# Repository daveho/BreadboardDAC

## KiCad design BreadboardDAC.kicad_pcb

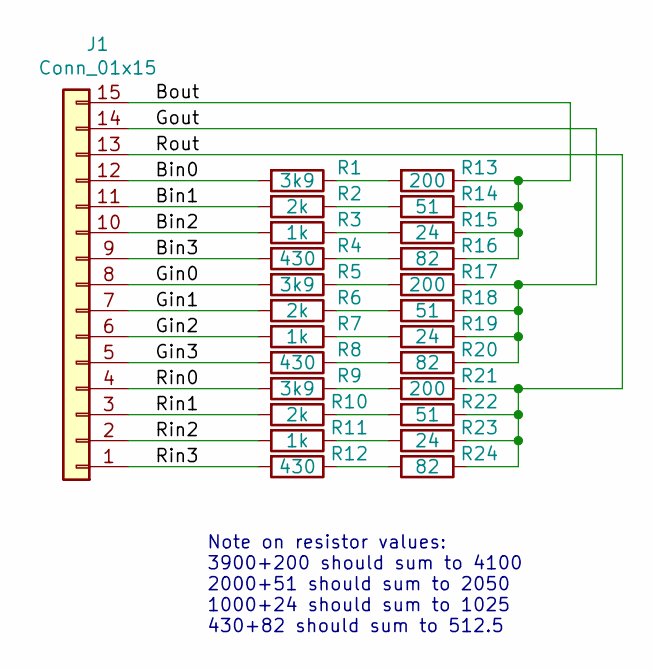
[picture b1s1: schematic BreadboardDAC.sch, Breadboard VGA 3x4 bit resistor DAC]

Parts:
J1: Conn_01x15; PinHeader_1x15_P2.54mm_Vertical
R1, R5, R9: 3k9; R_Axial_DIN0204_L3.6mm_D1.6mm_P2.54mm_Vertical
R2, R6, R10: 2k; R_Axial_DIN0204_L3.6mm_D1.6mm_P2.54mm_Vertical
R3, R7, R11: 1k; R_Axial_DIN0204_L3.6mm_D1.6mm_P2.54mm_Vertical
R4, R8, R12: 430; R_Axial_DIN0204_L3.6mm_D1.6mm_P2.54mm_Vertical
R13, R17, R21: 200; R_Axial_DIN0204_L3.6mm_D1.6mm_P2.54mm_Vertical
R14, R18, R22: 51; R_Axial_DIN0204_L3.6mm_D1.6mm_P2.54mm_Vertical
R15, R19, R23: 24; R_Axial_DIN0204_L3.6mm_D1.6mm_P2.54mm_Vertical
R16, R20, R24: 82; R_Axial_DIN0204_L3.6mm_D1.6mm_P2.54mm_Vertical

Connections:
/Bin0: J1.12, R1.2
/Bin1: J1.11, R2.2
/Bin2: J1.10, R3.2
/Bin3: J1.9, R4.2
/Bout: J1.15, R13.1, R14.1, R15.1, R16.1
/Gin0: J1.8, R5.2
/Gin1: J1.7, R6.2
/Gin2: J1.6, R7.2
/Gin3: J1.5, R8.2
/Gout: J1.14, R17.1, R18.1, R19.1, R20.1
/Rin0: J1.4, R9.2
/Rin1: J1.3, R10.2
/Rin2: J1.2, R11.2
/Rin3: J1.1, R12.2
/Rout: J1.13, R21.1, R22.1, R23.1, R24.1
unnamed: R1.1, R13.2
unnamed: R10.1, R22.2
unnamed: R11.1, R23.2
unnamed: R12.1, R24.2
unnamed: R2.1, R14.2
unnamed: R3.1, R15.2
unnamed: R4.1, R16.2
unnamed: R5.1, R17.2
unnamed: R6.1, R18.2
unnamed: R7.1, R19.2
unnamed: R8.1, R20.2
unnamed: R9.1, R21.2

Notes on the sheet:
Note on resistor values: 3900+200 should sum to 4100 2000+51 should sum to 2050 1000+24 should sum to 1025 430+82 should sum to 512.5

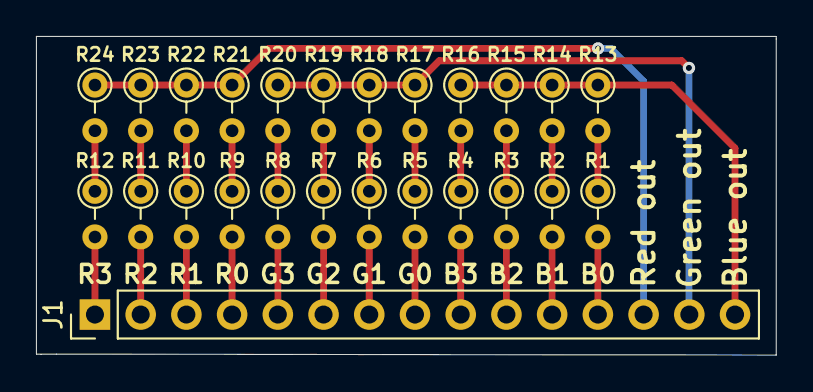
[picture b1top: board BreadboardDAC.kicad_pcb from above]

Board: 2 copper layers, 41.1 x 17.7 mm, 25 parts (0 on the bottom side), 27 nets.

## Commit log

2021-09-11 initial checkin
2021-09-11 fix footprint association for pin header
2021-09-11 use vertical orientation for resistors
2021-09-11 completed design?
